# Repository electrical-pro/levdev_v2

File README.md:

# levdev_v2
KiCAD PCB files for magnetic levitation device v2.0

PCB files provided as is, without any guarantee.
Check for mistakes if needed. I did it for myself, and it works, but I am not professional PCB maker.
Moreover it is my first KiCAD project.

Video about this device: https://youtu.be/cSmC9j-Mq4M

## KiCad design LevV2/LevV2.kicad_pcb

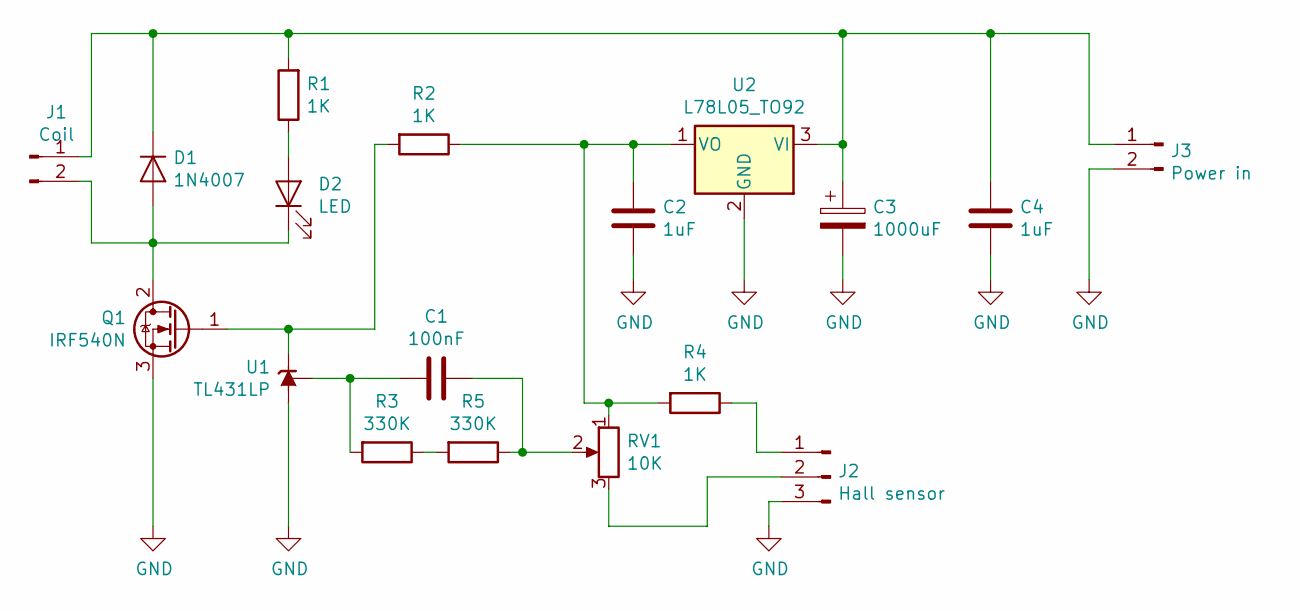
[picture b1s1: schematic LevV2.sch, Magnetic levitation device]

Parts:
C1: 100nF; C_0805_2012Metric_Pad1.15x1.40mm_HandSolder
C2, C4: 1uF; C_0805_2012Metric_Pad1.15x1.40mm_HandSolder
C3: 1000uF; CP_Radial_D10.0mm_P5.00mm
D1: 1N4007; D_DO-41_SOD81_P10.16mm_Horizontal
D2: LED; LED_D5.0mm
J1: Coil; SolderWirePad_1x02_P5.08mm_Drill1.5mm
J2: Hall sensor; PinSocket_1x03_P2.54mm_Vertical
J3: Power in; SolderWirePad_1x02_P5.08mm_Drill1.5mm
Q1: IRF540N; TO-220-3_Vertical
R1, R2, R4: 1K; R_0805_2012Metric_Pad1.15x1.40mm_HandSolder
R3, R5: 330K; R_0805_2012Metric_Pad1.15x1.40mm_HandSolder
RV1: 10K; Potentiometer_Bourns_3296W_Vertical
U1: TL431LP; TO-92_Inline
U2: L78L05_TO92; TO-92_Inline

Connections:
GND: C2.2, C3.2, C4.2, J2.3, J3.2, Q1.3 (S), U1.2 (A), U2.2 (GND)
unnamed: C1.1, R5.1, RV1.2
unnamed: C1.2, R3.2, U1.1 (REF)
unnamed: C2.1, R2.1, R4.2, RV1.1, U2.1 (VO)
unnamed: C3.1, C4.1, D1.1 (K), J1.1, J3.1, R1.2, U2.3 (VI)
unnamed: D1.2 (A), D2.1 (K), J1.2, Q1.2 (D)
unnamed: D2.2 (A), R1.1
unnamed: J2.1, R4.1
unnamed: J2.2, RV1.3
unnamed: Q1.1 (G), R2.2, U1.3 (K)
unnamed: R3.1, R5.2

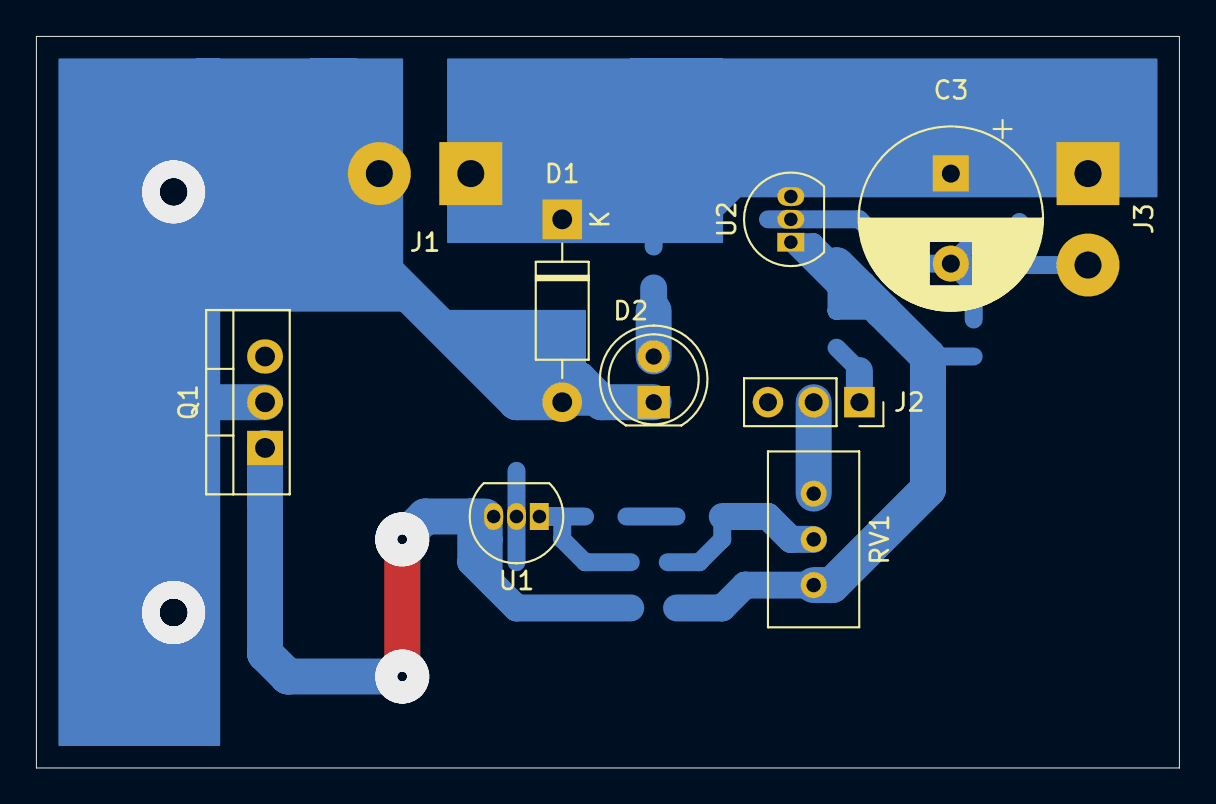
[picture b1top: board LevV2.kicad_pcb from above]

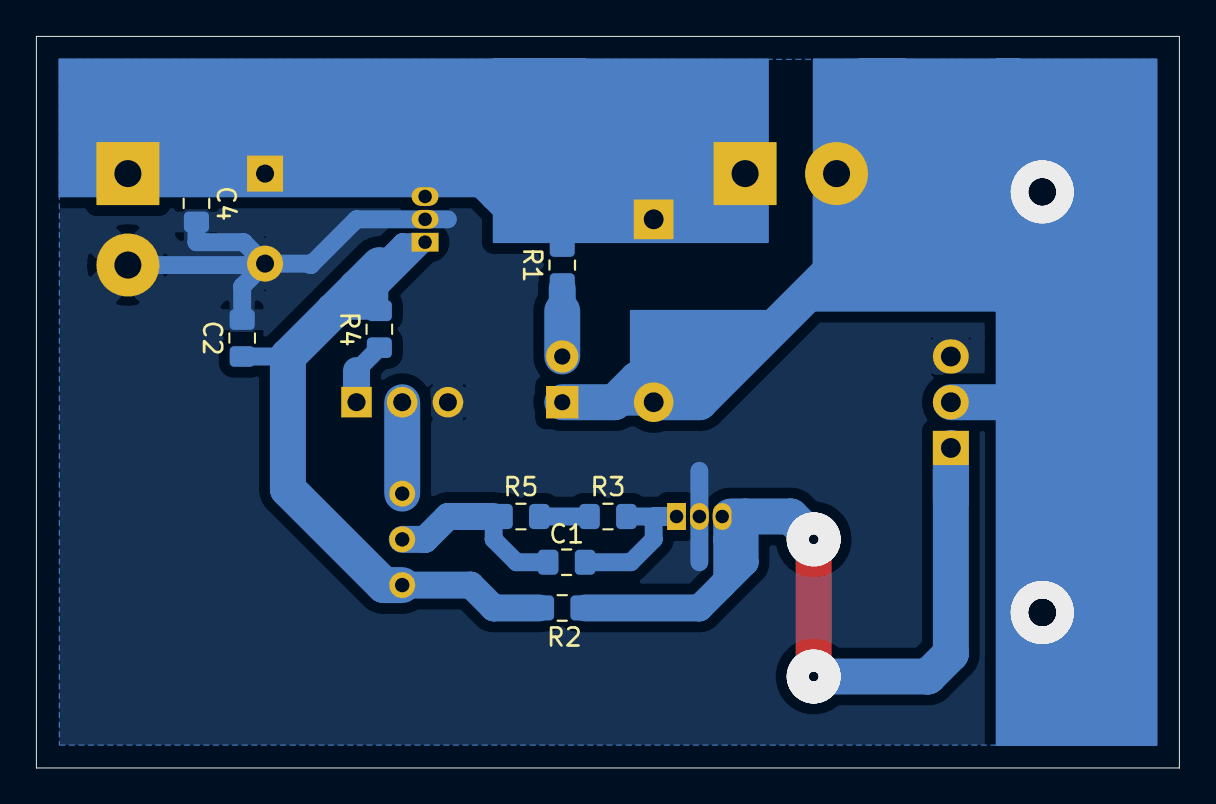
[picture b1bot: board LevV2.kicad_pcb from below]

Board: 2 copper layers, 63.5 x 40.6 mm, 18 parts (8 on the bottom side), 11 nets.
